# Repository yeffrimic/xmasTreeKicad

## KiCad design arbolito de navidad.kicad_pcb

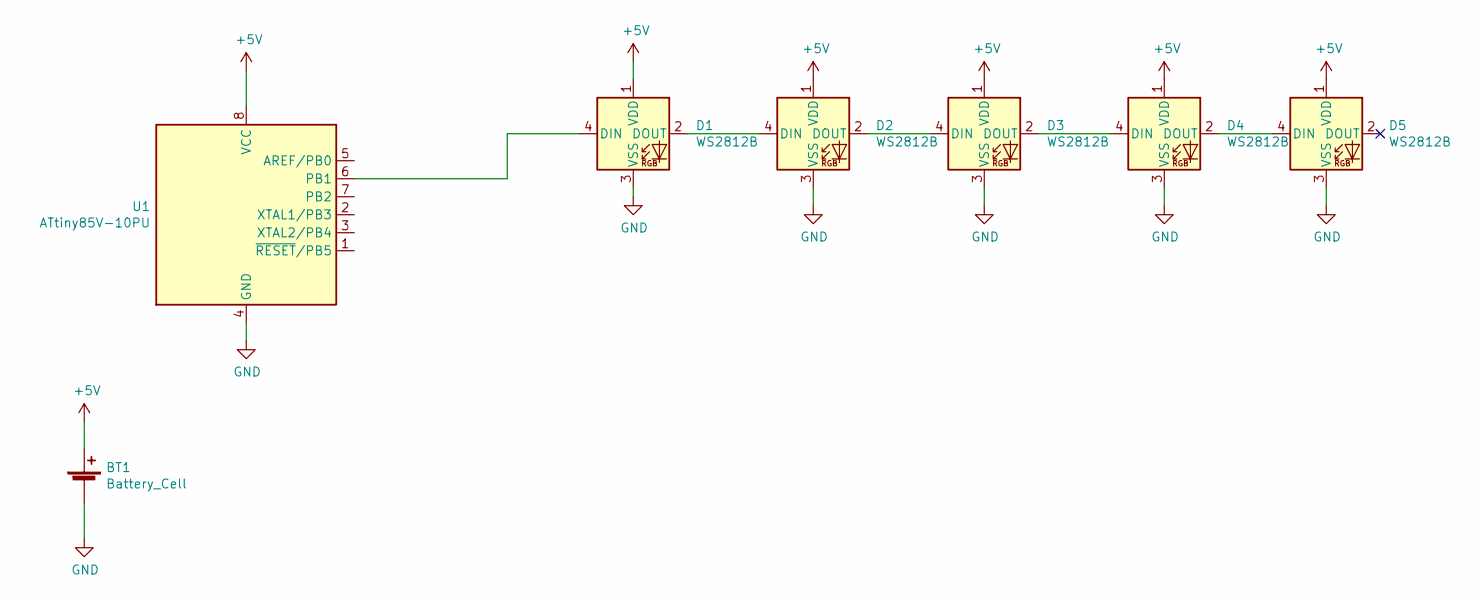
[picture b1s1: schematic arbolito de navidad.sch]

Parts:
BT1: Battery_Cell; PinHeader_1x02_P1.27mm_Vertical
D1, D2, D3, D4, D5: WS2812B; LED_WS2812B_PLCC4_5.0x5.0mm_P3.2mm
U1: ATtiny85V-10PU; DIP-8_W7.62mm

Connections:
+5V: BT1.1 (+), D1.1 (VDD), D2.1 (VDD), D3.1 (VDD), D4.1 (VDD), D5.1 (VDD), U1.8 (VCC)
GND: BT1.2 (-), D1.3 (VSS), D2.3 (VSS), D3.3 (VSS), D4.3 (VSS), D5.3 (VSS), U1.4 (GND)
unnamed: D1.2 (DOUT), D2.4 (DIN)
unnamed: D1.4 (DIN), U1.6 (PB1)
unnamed: D2.2 (DOUT), D3.4 (DIN)
unnamed: D3.2 (DOUT), D4.4 (DIN)
unnamed: D4.2 (DOUT), D5.4 (DIN)

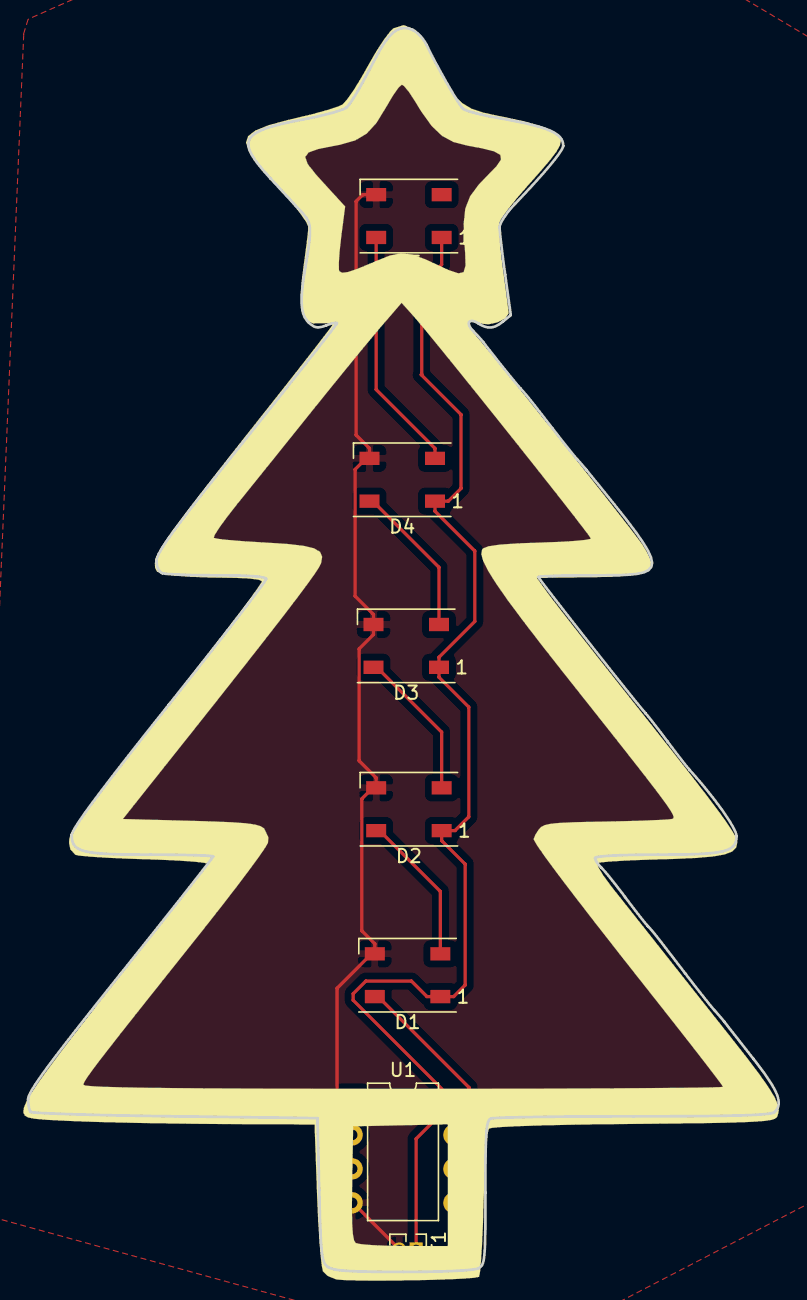
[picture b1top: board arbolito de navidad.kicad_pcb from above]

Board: 2 copper layers, 56.2 x 93.1 mm, 7 parts (0 on the bottom side), 7 nets.
